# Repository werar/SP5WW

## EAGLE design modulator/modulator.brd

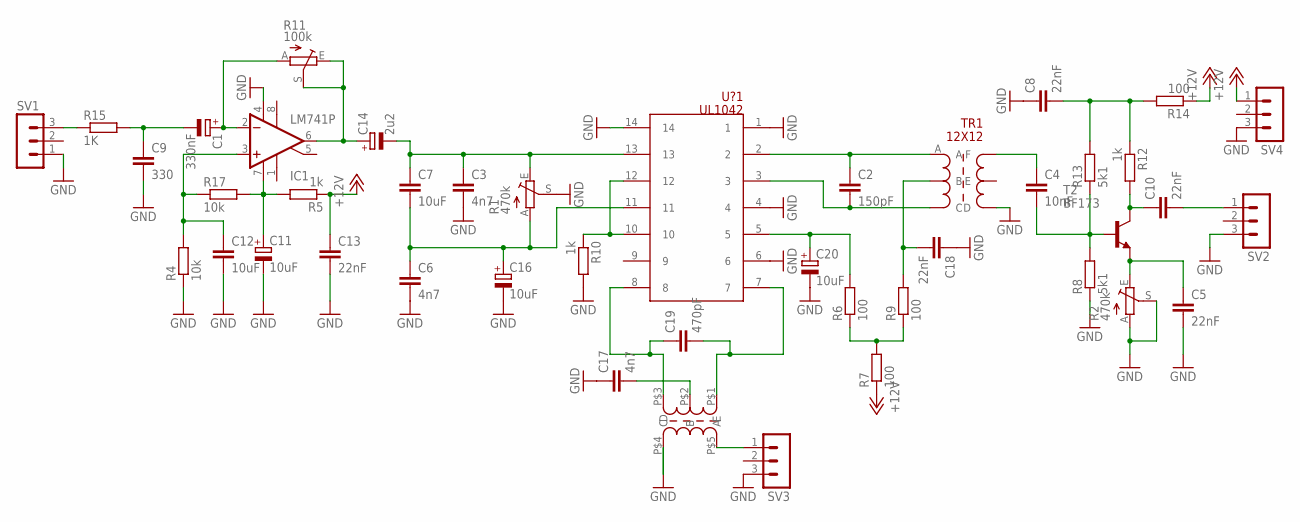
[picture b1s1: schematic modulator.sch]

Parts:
C1: 330nF; E2,5-5
C2: 150pF; C050-025X075
C3, C6, C17: 4n7; C050-025X075
C4: 10nF; C050-025X075
C5, C8, C10, C13, C18: 22nF; C050-025X075
C7, C12: 10uF; C050-025X075
C9: 330; C050-025X075
C11, C16, C20: 10uF; E2,5-5
C14: 2u2; E2,5-5
C19: 470pF; C050-025X075
IC1: LM741P; DIL08
R1: 470k; S64Y
R2: 470k; CA6V
R4, R17: 10k; 0204/7
R5, R10, R12: 1k; 0204/7
R6, R7, R9, R14: 100; 0204/7
R8, R13: 5k1; 0204/7
R11: 100k; CA6V
R15: 1K; 0204/7
SV1, SV2, SV3, SV4: MA03-1
T2: BF173; TO72
TR1: 12X12
TR2: TR5X5
U?1: UL1042; DIL14

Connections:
+12V: C13.1, R5.1, R7.1, R14.1, SV4.1
GND: C3.2, C5.2, C6.2, C8.1, C9.2, C11.-, C12.2, C13.2, C16.-, C17.1, C18.1, C20.-, IC1.4 (V-), R1.S, R2.A, R2.S, R4.1, R8.1, R10.2, SV1.1, SV2.3, SV3.3, SV4.3, TR1.D, TR1.GND1 (GND), TR1.GND2 (GND), TR2.P$4 (D), U?1.1, U?1.4, U?1.6, U?1.14
unnamed: C1.+, IC1.2 (-IN), R11.A
unnamed: C12.1, IC1.3 (+IN), R4.2, R17.1
unnamed: C1.-, C9.1, R15.2
unnamed: C11.+, IC1.7 (V+), R5.2, R17.2
unnamed: C3.1, C7.1, C14.-, R1.E, U?1.13
unnamed: C14.+, IC1.6 (OUT), R11.E, R11.S
unnamed: R10.1, U?1.10, U?1.12
unnamed: C6.1, C7.2, C16.+, R1.A, U?1.11
unnamed: C2.1, TR1.A, U?1.2
unnamed: C2.2, TR1.C, U?1.3
unnamed: C20.+, R6.2, U?1.5
unnamed: C17.2, TR2.P$2 (B)
unnamed: C4.2, R8.2, R13.1, T2.3 (B)
unnamed: C8.2, R12.1, R13.2, R14.2
unnamed: C19.1, TR2.P$3 (C), U?1.8
unnamed: C19.2, TR2.P$1 (A), U?1.7
unnamed: C10.1, R12.2, T2.2 (C)
unnamed: R6.1, R7.2, R9.1
unnamed: C5.1, R2.E, T2.4 (E)
unnamed: C18.2, R9.2, TR1.B
unnamed: SV3.1, TR2.P$5 (E)
unnamed: C10.2, SV2.1
unnamed: R15.1, SV1.3
unnamed: C4.1, TR1.G (F)

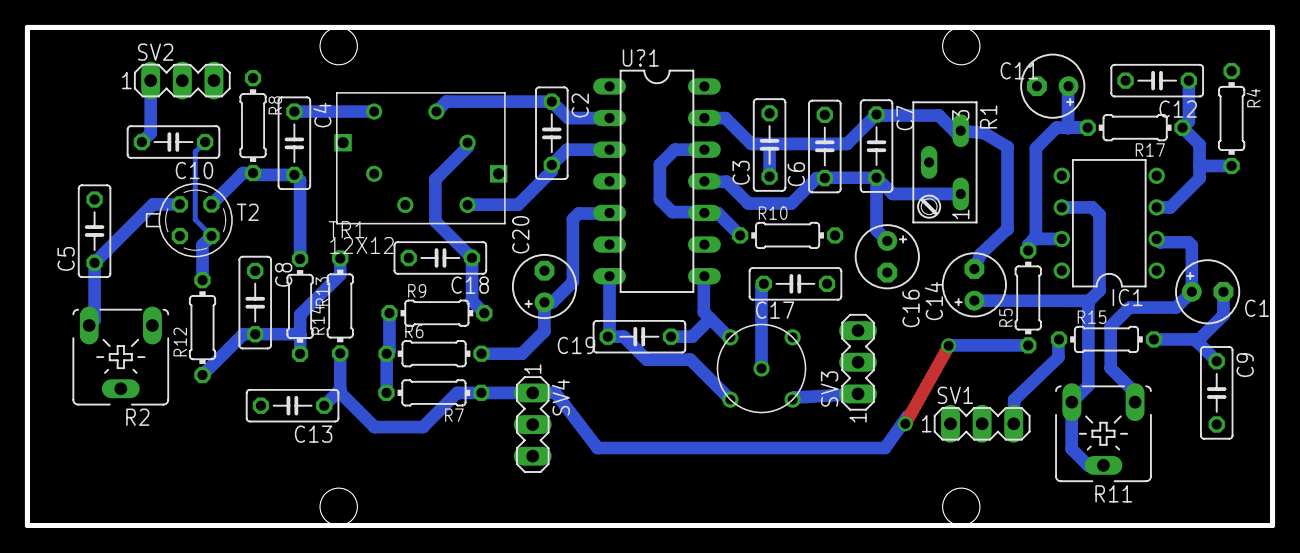
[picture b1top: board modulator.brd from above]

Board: 2 copper layers, 100.0 x 40.0 mm, 43 parts (0 on the bottom side), 26 nets.

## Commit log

2017-02-02 first version
2017-02-02 libs added
2017-02-02 added licence and readme
2017-02-03 rearrange the elements on the PCB.
